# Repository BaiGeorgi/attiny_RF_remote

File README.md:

# attiny_RF_remote
Attiny garage door remote that can be integrated inside a car.

The PCB will send RC code when you power it for a second and blink a led (that is optional).

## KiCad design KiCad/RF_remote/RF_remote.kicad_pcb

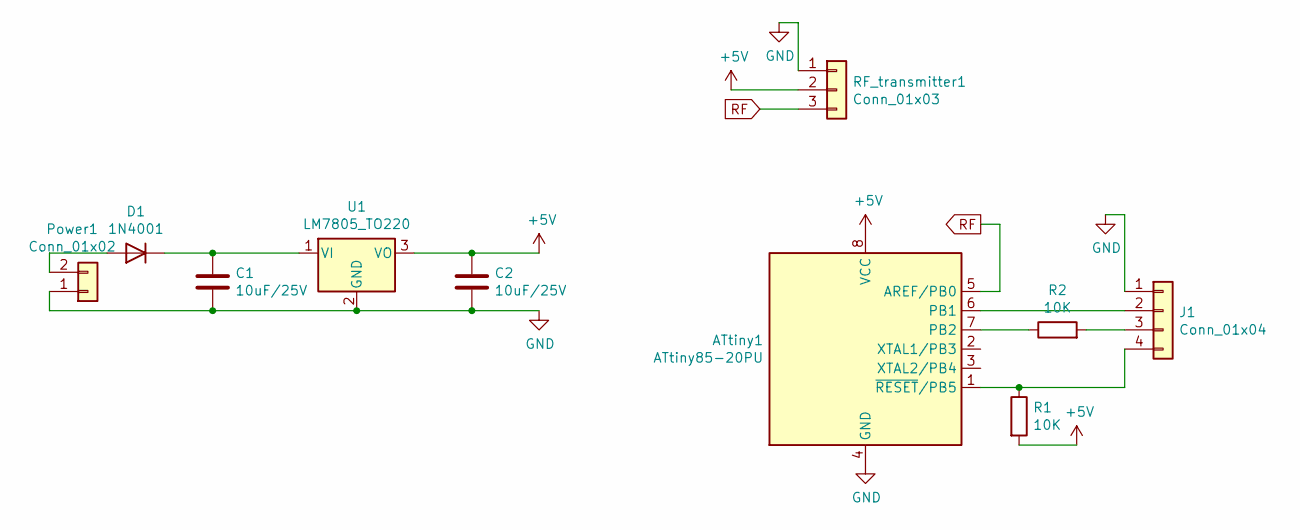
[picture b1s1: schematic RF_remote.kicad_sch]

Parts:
ATtiny1: ATtiny85-20PU; DIP-8_W7.62mm
C1, C2: 10uF/25V; C_Disc_D8.0mm_W2.5mm_P5.00mm
D1: 1N4001; D_DO-41_SOD81_P10.16mm_Horizontal
J1: Conn_01x04; PinHeader_1x04_P2.54mm_Vertical
Power1: Conn_01x02; PinHeader_1x02_P2.54mm_Vertical
R1, R2: 10K; R_Axial_DIN0207_L6.3mm_D2.5mm_P7.62mm_Horizontal
RF_transmitter1: Conn_01x03; PinHeader_1x03_P2.54mm_Vertical
U1: LM7805_TO220; TO-220-3_Vertical

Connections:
+5V: ATtiny1.8 (VCC), C2.1, R1.2, RF_transmitter1.2, U1.3 (VO)
GND: ATtiny1.4 (GND), C1.2, C2.2, J1.1, Power1.1, RF_transmitter1.1, U1.2 (GND)
unnamed: ATtiny1.1 (~RESET/PB5), J1.4, R1.1
unnamed: ATtiny1.6 (PB1), J1.2
unnamed: ATtiny1.7 (PB2), R2.1
unnamed: C1.1, D1.1 (K), U1.1 (VI)
unnamed: D1.2 (A), Power1.2
unnamed: J1.3, R2.2
RF: ATtiny1.5 (AREF/PB0), RF_transmitter1.3

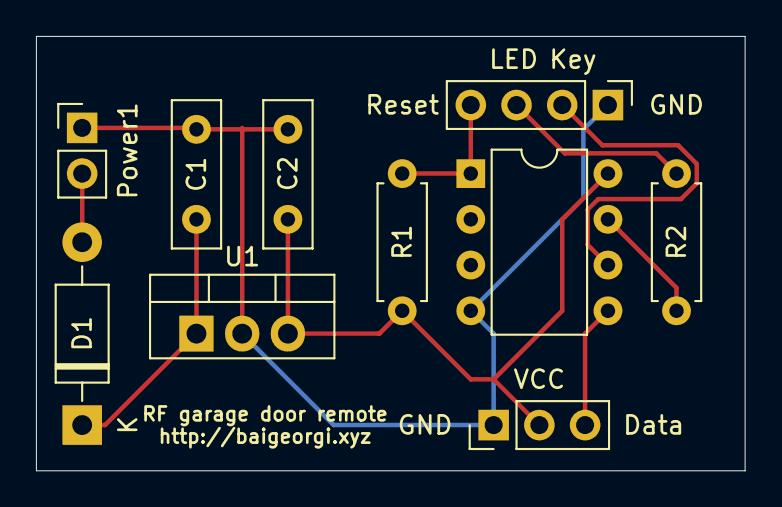
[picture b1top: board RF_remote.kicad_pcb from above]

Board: 2 copper layers, 39.4 x 24.1 mm, 10 parts (0 on the bottom side), 9 nets.

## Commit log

2022-07-02 Added photos
2022-07-02 Updated images
2022-07-02 too big
2022-07-18 Image with the schematic.
2022-07-18 description
